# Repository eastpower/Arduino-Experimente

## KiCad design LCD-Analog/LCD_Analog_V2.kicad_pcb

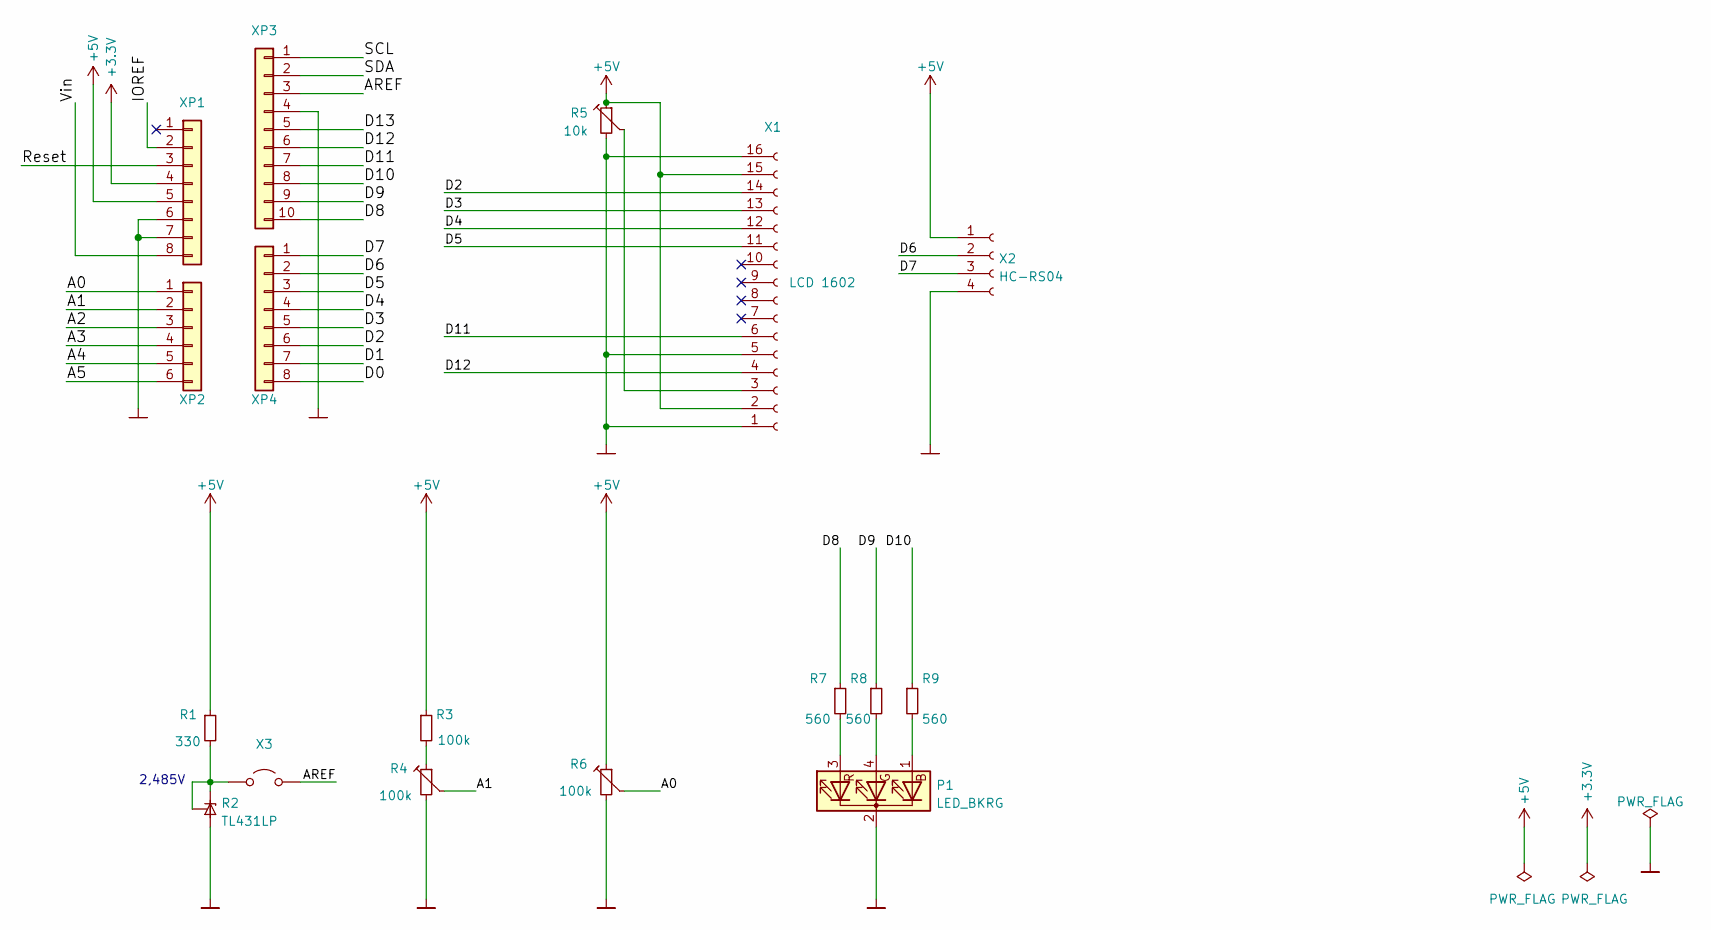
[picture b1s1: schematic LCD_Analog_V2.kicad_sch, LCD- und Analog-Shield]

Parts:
P1: LED_BKRG; LED_D5.0mm-4_RGB
R1: 330; R_Axial_DIN0207_L6.3mm_D2.5mm_P10.16mm_Horizontal
R2: TL431LP; TO-92_Inline
R3: 100k; R_Axial_DIN0207_L6.3mm_D2.5mm_P10.16mm_Horizontal
R4, R6: 100k; Potentiometer_Piher_PT-10-V10_Vertical
R5: 10k; Potentiometer_Piher_PT-10-V10_Vertical
R7, R8, R9: 560; R_Axial_DIN0207_L6.3mm_D2.5mm_P10.16mm_Horizontal
X1: LCD 1602; PinSocket_1x16_P2.54mm_Vertical
X2: HC-RS04; PinSocket_1x04_P2.54mm_Vertical
X3: Jumper_2_Open; TestPoint_2Pads_Pitch2.54mm_Drill0.8mm
XP1: Power; Socket_Strip_Arduino_1x08
XP2: Analog; Socket_Strip_Arduino_1x06
XP3: Digital; Socket_Strip_Arduino_1x10
XP4: Digital; Socket_Strip_Arduino_1x08

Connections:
+3V3: XP1.4
+5V: R1.1, R3.1, R5.1, R6.1, X1.2, X1.15, X2.1, XP1.5
/A0: R6.2, XP2.1
/A1: R4.2, XP2.2
/A2: XP2.3
/A3: XP2.4
/A4: XP2.5
/A5: XP2.6
/AREF: X3.2 (B), XP3.3
/D0: XP4.8
/D1: XP4.7
/D2: X1.14, XP4.6
/D3: X1.13, XP4.5
/D4: X1.12, XP4.4
/D5: X1.11, XP4.3
/D6: X2.2, XP4.2
/D7: X2.3, XP4.1
/D8: R7.1, XP3.10
/D9: R8.1, XP3.9
/D10: R9.1, XP3.8
/D11: X1.6, XP3.7
/D12: X1.4, XP3.6
/D13: XP3.5
/IOREF: XP1.2
/Reset: XP1.3
/SCL: XP3.1
/SDA: XP3.2
/Vin: XP1.8
GND: P1.2 (K), R2.2 (A), R4.3, R5.3, R6.3, X1.1, X1.5, X1.16, X2.4, XP1.6, XP1.7, XP3.4
unnamed: P1.1 (BA), R9.2
unnamed: P1.3 (RA), R7.2
unnamed: P1.4 (GA), R8.2
unnamed: R1.2, R2.1 (REF), R2.3 (K), X3.1 (A)
unnamed: R3.2, R4.1
unnamed: R5.2, X1.3

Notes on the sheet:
2,485V

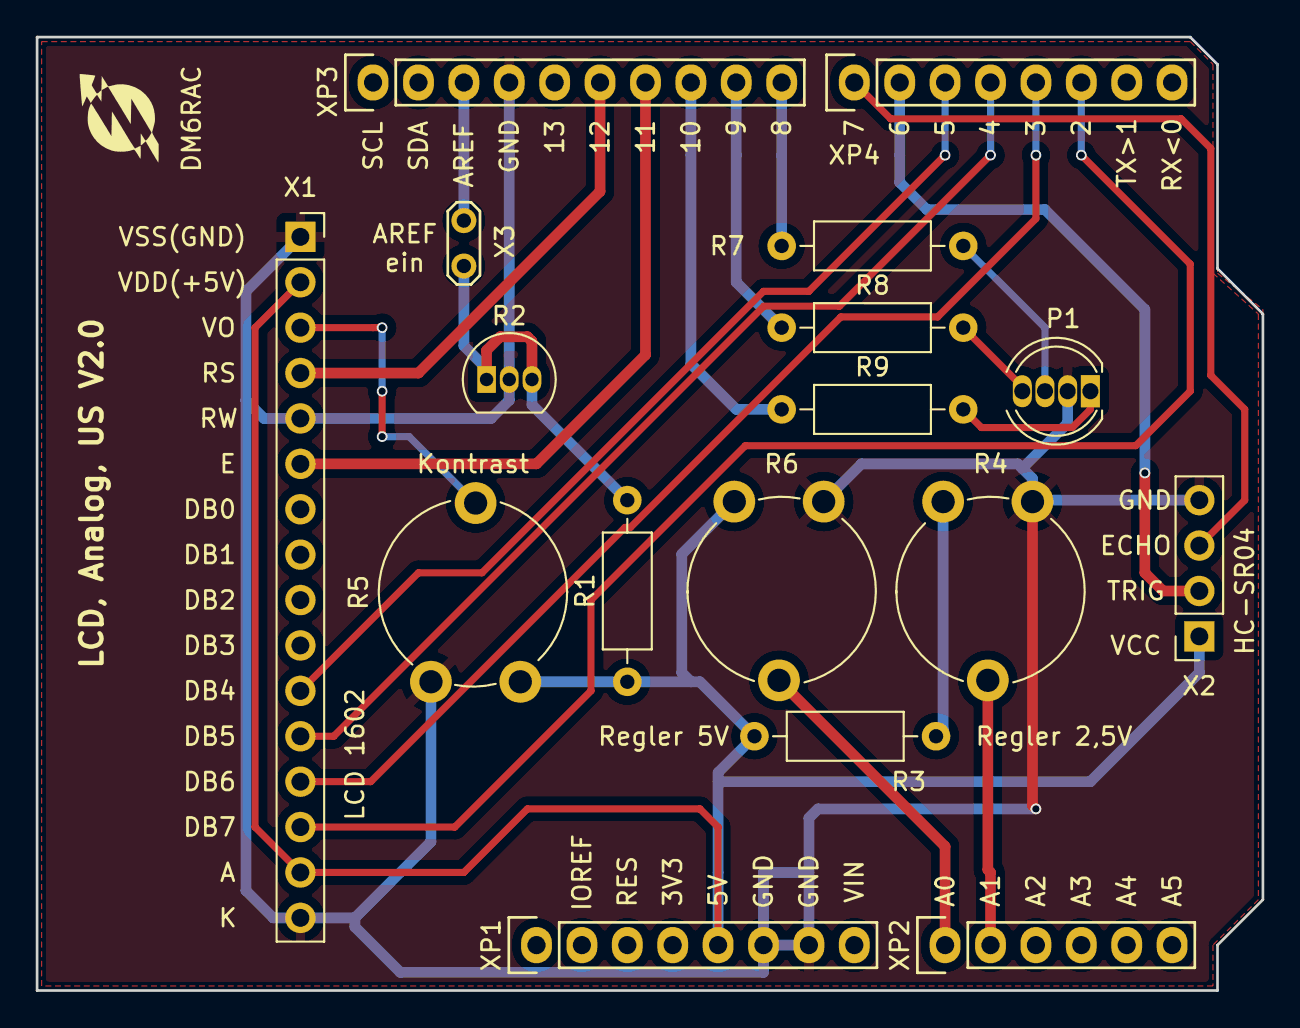
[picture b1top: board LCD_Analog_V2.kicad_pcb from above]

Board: 2 copper layers, 68.6 x 53.3 mm, 17 parts (0 on the bottom side), 22 nets.

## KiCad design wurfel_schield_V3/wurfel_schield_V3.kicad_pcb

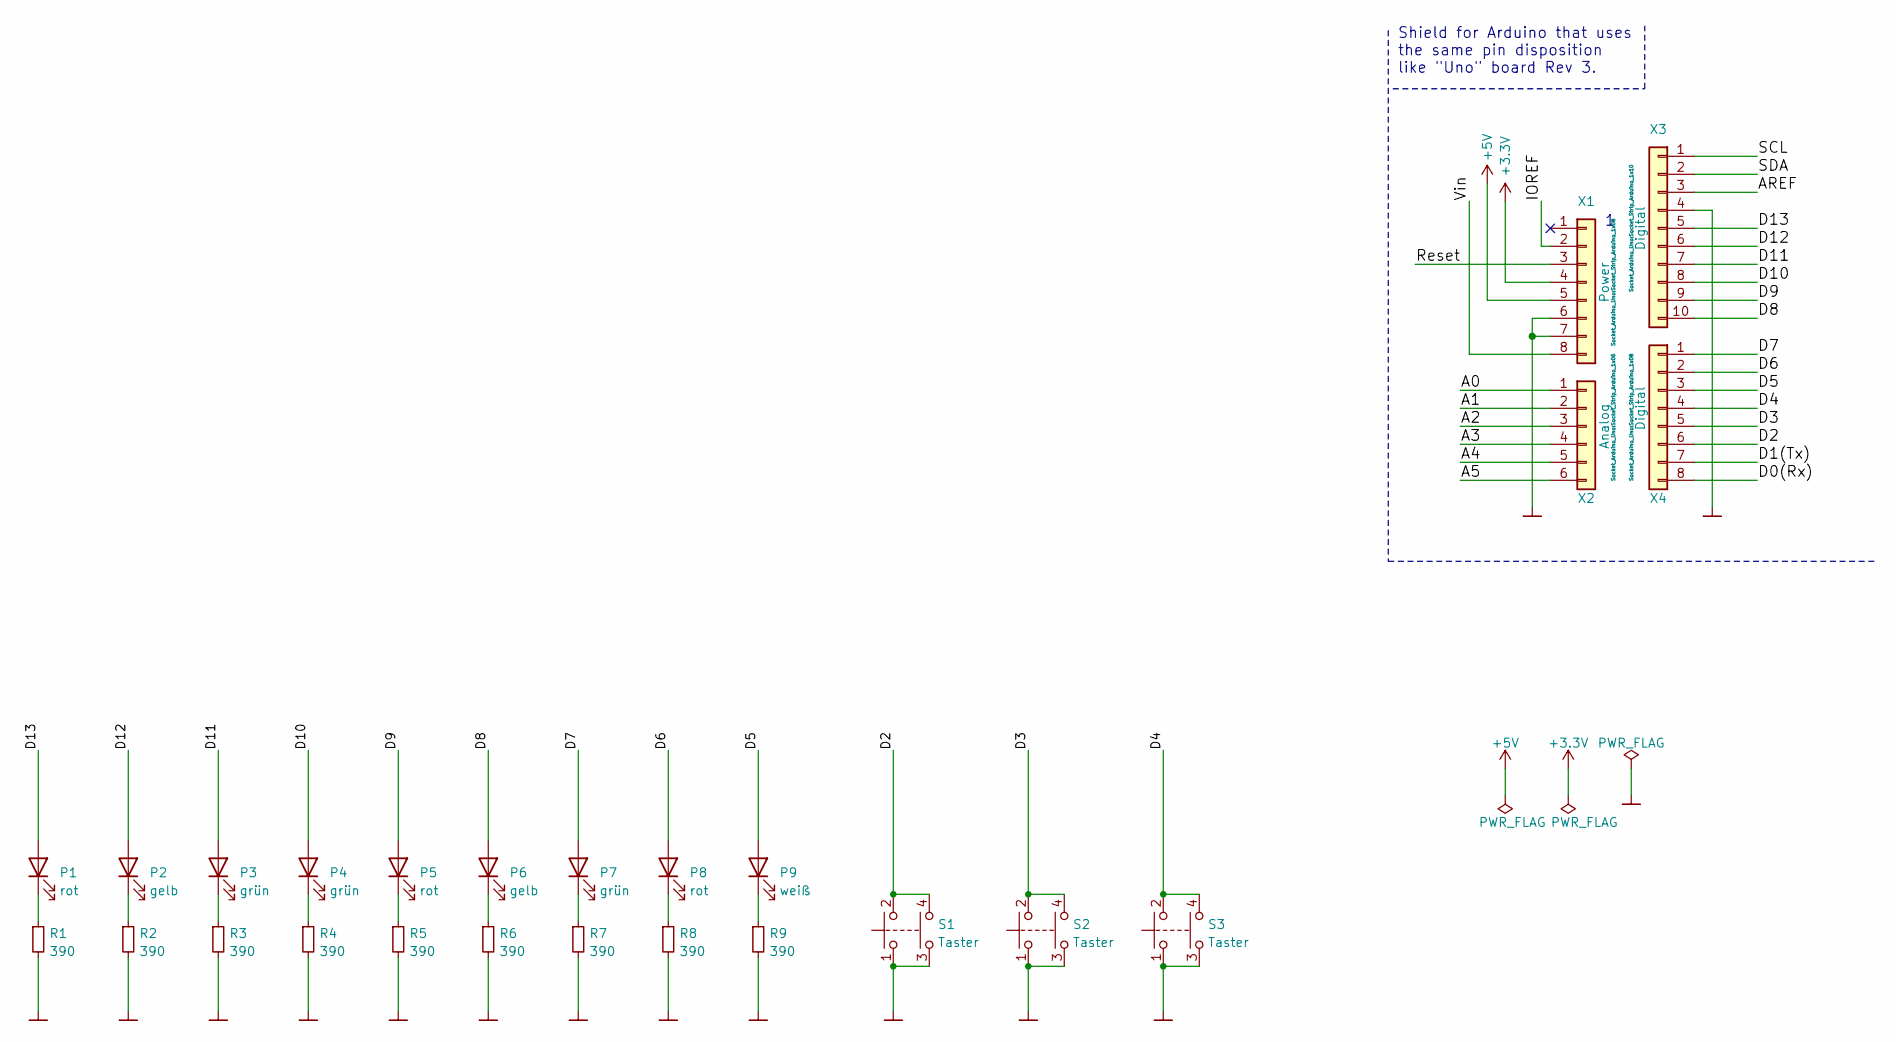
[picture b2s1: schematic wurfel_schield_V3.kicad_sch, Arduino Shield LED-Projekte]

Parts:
P1, P5, P8: rot; LED_D5.0mm
P2, P6: gelb; LED_D5.0mm
P3, P4, P7: grün; LED_D5.0mm
P9: weiß; LED_D5.0mm
R1, R2, R3, R4, R5, R6, R7, R8, R9: 390; R_Axial_DIN0207_L6.3mm_D2.5mm_P10.16mm_Horizontal
S1, S2, S3: Taster; SW_PUSH_6mm_H9.5mm
X1: Power; Socket_Strip_Arduino_1x08
X2: Analog; Socket_Strip_Arduino_1x06
X3: Digital; Socket_Strip_Arduino_1x10
X4: Digital; Socket_Strip_Arduino_1x08

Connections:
+3V3: X1.4
+5V: X1.5
/A0: X2.1
/A1: X2.2
/A2: X2.3
/A3: X2.4
/A4: X2.5
/A5: X2.6
/AREF: X3.3
/D0(Rx): X4.8
/D1(Tx): X4.7
/D2: S1.2, S1.4, X4.6
/D3: S2.2, S2.4, X4.5
/D4: S3.2, S3.4, X4.4
/D5: P9.2 (A), X4.3
/D6: P8.2 (A), X4.2
/D7: P7.2 (A), X4.1
/D8: P6.2 (A), X3.10
/D9: P5.2 (A), X3.9
/D10: P4.2 (A), X3.8
/D11: P3.2 (A), X3.7
/D12: P2.2 (A), X3.6
/D13: P1.2 (A), X3.5
/IOREF: X1.2
/Reset: X1.3
/SCL: X3.1
/SDA: X3.2
/Vin: X1.8
GND: R1.2, R2.2, R3.2, R4.2, R5.2, R6.2, R7.2, R8.2, R9.2, S1.1, S1.3, S2.1, S2.3, S3.1, S3.3, X1.6, X1.7, X3.4
unnamed: P1.1 (K), R1.1
unnamed: P2.1 (K), R2.1
unnamed: P3.1 (K), R3.1
unnamed: P4.1 (K), R4.1
unnamed: P5.1 (K), R5.1
unnamed: P6.1 (K), R6.1
unnamed: P7.1 (K), R7.1
unnamed: P8.1 (K), R8.1
unnamed: P9.1 (K), R9.1

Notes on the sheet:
Shield for Arduino that uses the same pin disposition like "Uno" board Rev 3.

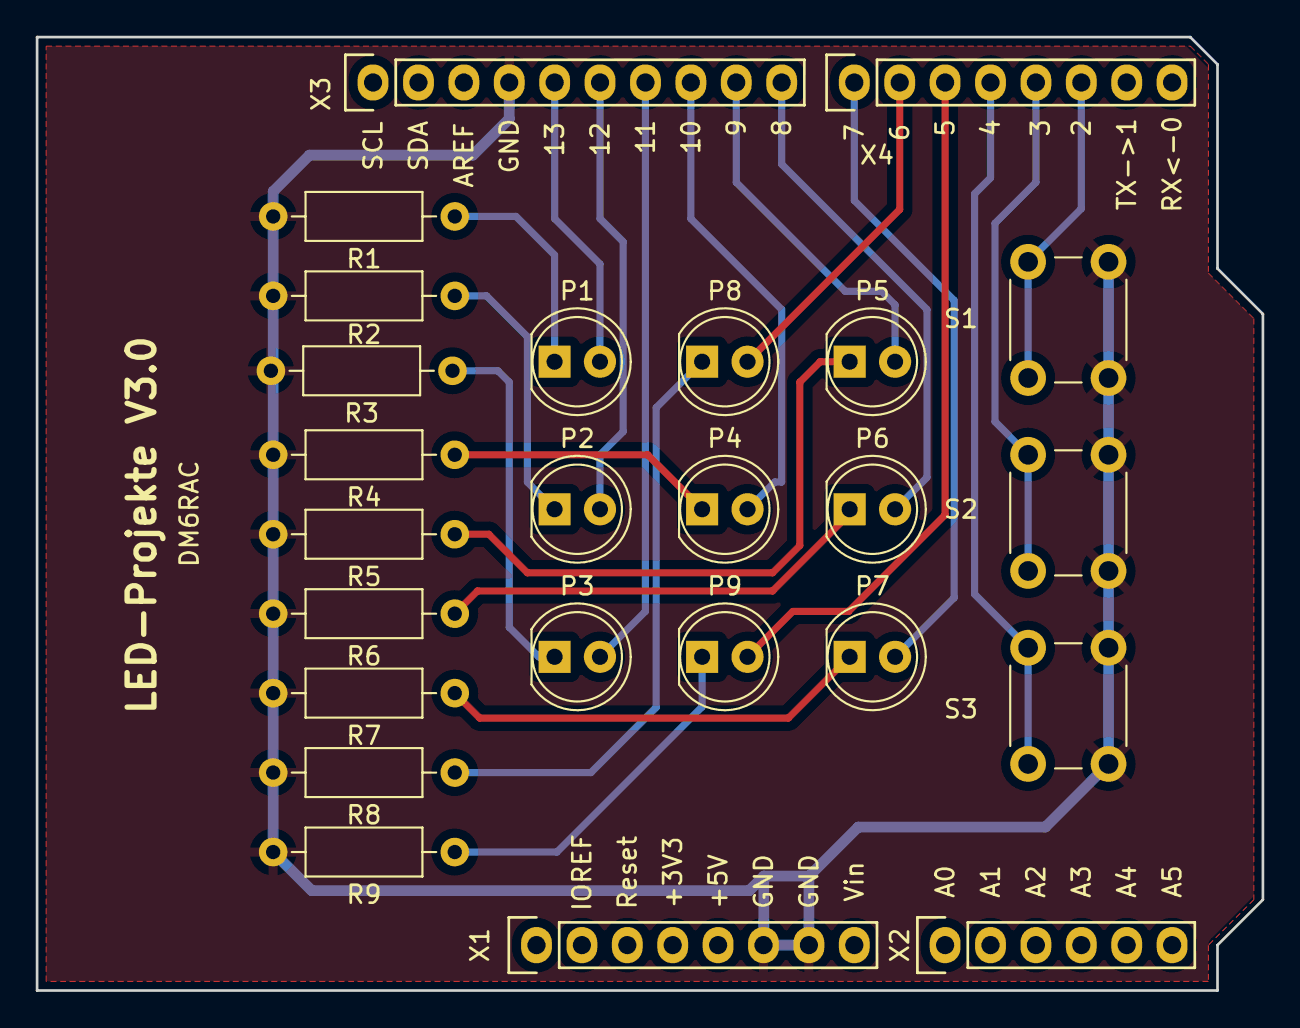
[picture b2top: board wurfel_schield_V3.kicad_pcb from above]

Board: 2 copper layers, 68.6 x 53.3 mm, 25 parts (0 on the bottom side), 22 nets.

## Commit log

2022-12-30 Template
2022-12-30 Create LICENSE
2023-01-04 LCD-Analog
2023-01-04 EUPL_1.2_DE
2023-01-19 Software
